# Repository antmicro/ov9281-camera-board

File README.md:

# OV9281 Dual camera board

Copyright (c) 2019-2023 [Antmicro](https://www.antmicro.com)

## Overview

This project contains open hardware design files for a dual camera module equipped with a pair of 1-megapixel [OmniVision OV9281](https://www.ovt.com/sensors/OV9281) image sensors.
The board includes mounting holes for standard S-Mount (M12) lens holders.
Each image sensor can be connected to a host platform via a separate 2-lane MIPI CSI-2 interface.
The PCB design files were prepared in KiCad 6.x.

## Key Features

* Two monochrome global shutter sensors OV9281
 
  * Pixel size: 3μm x 3 μm
  * Active array size: 1280 x 800 px
  * Optical size: 1/4 inch
  * Output formats: 8/10-bit BW RAW
  * Maximum image transfer rate: 1280 x 800 @60 fps

## Project structure 

The  main directory contains KiCad PCB project files, a LICENSE and a README. 
The remaining files are stored in the following directories: 

* `lib` - contains the component libraries 
* `img` - contains graphics for this readme 
* `assets` - contains visual assets for showcasing this design on [Open Hardware Portal](https://openhardware.antmicro.com).

The board exposes MIPI CSI-2 interfaces using unified 50-pin connector that is electrically compatible with a variety of video processing platforms created by Antmicro: 

* [Jeston Orin Baseboard](https://github.com/antmicro/jetson-orin-baseboard)
* [Jetson Nano Baseboard](https://github.com/antmicro/jetson-nano-baseboard)
* [Snapdragon 845 Baseboard](https://github.com/antmicro/snapdragon-845-baseboard)
* [Kria K26 Devboard](https://github.com/antmicro/kria-k26-devboard)

## Licensing

This project is published under the [Apache-2.0](LICENSE) license.

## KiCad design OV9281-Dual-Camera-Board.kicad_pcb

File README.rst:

========================
OV9281 Dual camera board
========================

Copyright (c) 2019-2021 `Antmicro <https://www.antmicro.com>`_

.. Image:: img/ov9281-board-photo.jpg

Overview
========

This repository contains open hardware design files for a dual camera module created by `Antmicro <https://antmicro.com/>`_.
This board is equipped with a pair of 1-megapixel `OmniVision OV9281 <https://www.ovt.com/sensors/OV9281>`_ image sensors with mounting holes for standard S-Mount (M12) lens holders.
Each sensor can be connected to a host platform via a separate 2-lane MIPI CSI-2 interface.
The PCB design files have been written in KiCad and released as Open Source Hardware (OSHW).

Key Features
============

+------------------------------+--------------------------------------+
| Image sensor(s):             | 2 x monochrome global shutter OV9281 |
+------------------------------+--------------------------------------+
| Pixel size:                  | 3μm x 3 μm                           |
+------------------------------+--------------------------------------+
| Active array size:           | 1280 x 800                           |
+------------------------------+--------------------------------------+
| Optical size:                | 1/4 inch                             |
+------------------------------+--------------------------------------+
| Lens mount:                  | M-12 (S-Mount)                       |
+------------------------------+--------------------------------------+
| Output interface:            | 50-pin FFC connector                 |
+------------------------------+--------------------------------------+
| Output formats:              | 8/10-bit BW RAW                      |
+------------------------------+--------------------------------------+
| Maximum image transfer rate: | 1280 x 800 @60 fps                   |
+------------------------------+--------------------------------------+

Interface connector
===================

The board uses a 50-pin FFC connector which exposes two separate MIPI CSI interfaces for both cameras, along with power supply rails and separate I2C buses used for sensor configuration.
The board is electrically compatible with Antmicro's products and open hardware designs, including `Jetson Nano baseboard <https://github.com/antmicro/jetson-nano-baseboard>`_,
`Google Coral Baseboard <https://github.com/antmicro/google-coral-baseboard>`_ or `Zynq Video Board <https://github.com/antmicro/zynq-video-board>`_.

For more details regarding the on-board circuitry please refer to the respective schematic sheets.

Mechanics
=========

Board dimensions:

.. image:: img/ov9281-board-dimensions.png

License
=======

`Apache-2.0 <LICENSE>`_

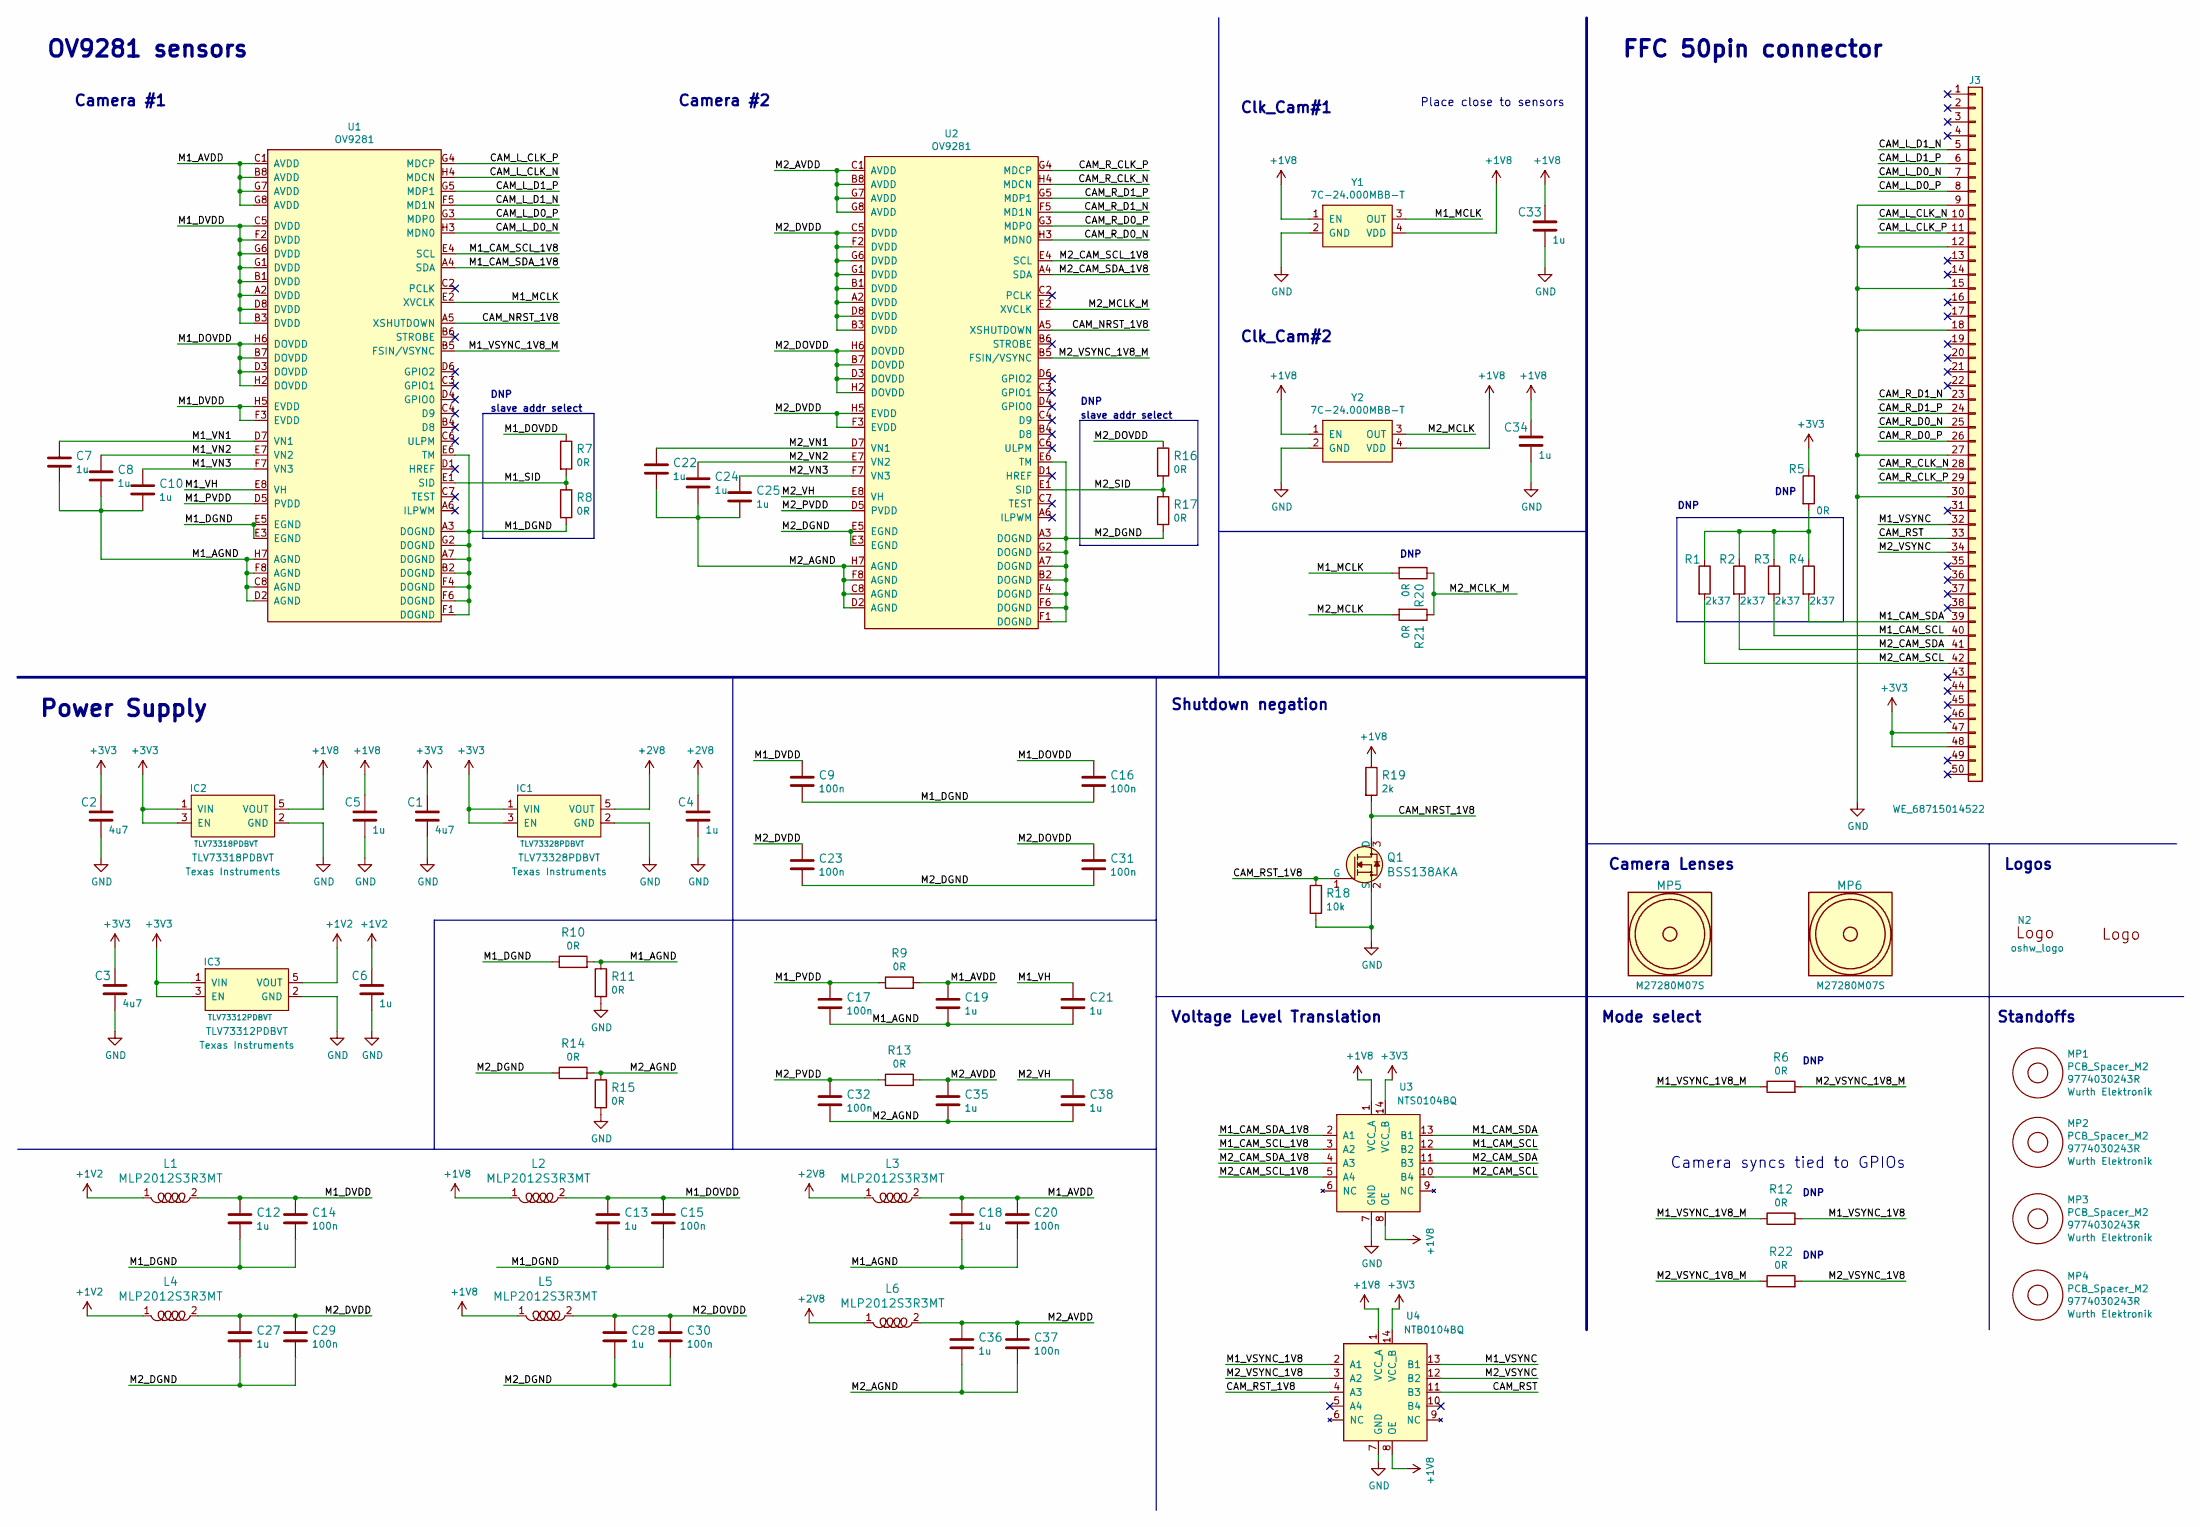
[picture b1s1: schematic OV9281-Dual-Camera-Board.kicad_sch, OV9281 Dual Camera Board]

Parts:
C1, C2, C3: C_4u7_0805; 0805-cap; MPN 0805X475K250CT
C4, C5, C6, C7, C8, C10, C12, C13, C18, C19, C21, C22, C24, C25, C27, C28, C33, C34, C35, C36, C38: C_1u_0603; 0603-cap; MPN 0603X105K160CT
C9, C14, C15, C16, C17, C20, C23, C29, C30, C31, C32, C37: C_100n_0402_6V3; 0402-cap; MPN 0402X104K6R3CT
IC1: TLV73328PDBVT; SOT-23-5; MPN TLV73328PDBVT
IC2: TLV73318PDBVT; SOT-23-5; MPN TLV73318PDBVT
IC3: TLV73312PDBVT; SOT-23-5; MPN TLV73312PDBVT
J3: WE_68715014522; MPN 68715014522
L1, L2, L3, L4, L5, L6: MLP2012S3R3MT; 0805-res; MPN MLP2012S3R3MT
MP1, MP2, MP3, MP4: PCB_Spacer_M2; 9774030243R; MPN 9774030243R
MP5, MP6: Camera_Lens; Camera_Lens_20mm_ARDUCAM_M27280M07S; MPN M27280M07S
N1: antmicro_logo; antmicro-logo_scaled_20mm
N2: oshw_logo; oshw-logo
Q1: BSS138AKA; SOT-23-3; MPN BSS138AKA
R1, R2, R3, R4: R_2k37_0402; 0402-res; MPN CRCW04022K37FKED
R5, R6, R7, R8, R9, R10, R11, R12, R13, R14, R15, R16, R17, R20, R21, R22: R_0R_0402; 0402-res; MPN ERJ2GE0R00X
R18: R_10k_0402; 0402-res; MPN CRCW040210K0FKEDHP
R19: R_2k_0402; 0402-res; MPN CRCW04022K00FKED
U1, U2: OV9281; ov9281; MPN OV9281
U3: NTS0104BQ; QDHVQFN14; MPN NTS0104BQ
U4: NTB0104BQ; QDHVQFN14; MPN NTB0104BQ
Y1, Y2: 7C-24.000MBB-T; MPN 7C-24.000MBB-T

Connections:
+1V2: C6.1, IC3.5 (VOUT), L1.1, L4.1
+1V8: C5.1, C33.1, C34.1, IC2.5 (VOUT), L2.1, L5.1, R19.1, U3.1 (VCC_A), U3.8 (OE), U4.1 (VCC_A), U4.8 (OE), Y1.1 (EN), Y1.4 (VDD), Y2.1 (EN), Y2.4 (VDD)
+2V8: C4.1, IC1.5 (VOUT), L3.1, L6.1
+3V3: C1.1, C2.1, C3.1, IC1.1 (VIN), IC1.3 (EN), IC2.1 (VIN), IC2.3 (EN), IC3.1 (VIN), IC3.3 (EN), J3.47, J3.48, R5.1, U3.14 (VCC_B), U4.14 (VCC_B)
/CAM_L_CLK_N: J3.10, U1.H4 (MDCN)
/CAM_L_CLK_P: J3.11, U1.G4 (MDCP)
/CAM_L_D0_N: J3.7, U1.H3 (MDN0)
/CAM_L_D0_P: J3.8, U1.G3 (MDP0)
/CAM_L_D1_N: J3.5, U1.F5 (MD1N)
/CAM_L_D1_P: J3.6, U1.G5 (MDP1)
/CAM_NRST_1V8: Q1.3 (D), R19.2, U1.A5 (XSHUTDOWN), U2.A5 (XSHUTDOWN)
/CAM_RST: J3.33, U4.11 (B3)
/CAM_RST_1V8: Q1.1 (G), R18.1, U4.4 (A3)
/CAM_R_CLK_N: J3.28, U2.H4 (MDCN)
/CAM_R_CLK_P: J3.29, U2.G4 (MDCP)
/CAM_R_D0_N: J3.25, U2.H3 (MDN0)
/CAM_R_D0_P: J3.26, U2.G3 (MDP0)
/CAM_R_D1_N: J3.23, U2.F5 (MD1N)
/CAM_R_D1_P: J3.24, U2.G5 (MDP1)
/M1_AGND: C7.2, C8.2, C10.2, C17.2, C18.2, C19.2, C20.2, C21.2, R10.2, R11.1, U1.C8 (AGND), U1.D2 (AGND), U1.F8 (AGND), U1.H7 (AGND)
/M1_AVDD: C18.1, C19.1, C20.1, L3.2, R9.2, U1.B8 (AVDD), U1.C1 (AVDD), U1.G7 (AVDD), U1.G8 (AVDD)
/M1_CAM_SCL: J3.40, R3.2, U3.12 (B2)
/M1_CAM_SCL_1V8: U1.E4 (SCL), U3.3 (A2)
/M1_CAM_SDA: J3.39, R4.2, U3.13 (B1)
/M1_CAM_SDA_1V8: U1.A4 (SDA), U3.2 (A1)
/M1_DGND: C9.2, C12.2, C13.2, C14.2, C15.2, C16.2, R8.2, R10.1, U1.A3 (DOGND), U1.A7 (DOGND), U1.B2 (DOGND), U1.E3 (EGND), U1.E5 (EGND), U1.E6 (TM), U1.F1 (DOGND), U1.F4 (DOGND), U1.F6 (DOGND), U1.G2 (DOGND)
/M1_DOVDD: C13.1, C15.1, C16.1, L2.2, R7.1, U1.B7 (DOVDD), U1.D3 (DOVDD), U1.H2 (DOVDD), U1.H6 (DOVDD)
/M1_DVDD: C9.1, C12.1, C14.1, L1.2, U1.A2 (DVDD), U1.B1 (DVDD), U1.B3 (DVDD), U1.C5 (DVDD), U1.D8 (DVDD), U1.F2 (DVDD), U1.F3 (EVDD), U1.G1 (DVDD), U1.G6 (DVDD), U1.H5 (EVDD)
/M1_MCLK: R20.2, U1.E2 (XVCLK), Y1.3 (OUT)
/M1_PVDD: C17.1, R9.1, U1.D5 (PVDD)
/M1_SID: R7.2, R8.1, U1.E1 (SID)
/M1_VH: C21.1, U1.E8 (VH)
/M1_VN1: C7.1, U1.D7 (VN1)
/M1_VN2: C8.1, U1.E7 (VN2)
/M1_VN3: C10.1, U1.F7 (VN3)
/M1_VSYNC: J3.32, U4.13 (B1)
/M1_VSYNC_1V8: R12.2, U4.2 (A1)
/M1_VSYNC_1V8_M: R6.1, R12.1, U1.B5 (FSIN/VSYNC)
/M2_AGND: C22.2, C24.2, C25.2, C32.2, C35.2, C36.2, C37.2, C38.2, R14.2, R15.1, U2.C8 (AGND), U2.D2 (AGND), U2.F8 (AGND), U2.H7 (AGND)
/M2_AVDD: C35.1, C36.1, C37.1, L6.2, R13.2, U2.B8 (AVDD), U2.C1 (AVDD), U2.G7 (AVDD), U2.G8 (AVDD)
/M2_CAM_SCL: J3.42, R1.2, U3.10 (B4)
/M2_CAM_SCL_1V8: U2.E4 (SCL), U3.5 (A4)
/M2_CAM_SDA: J3.41, R2.2, U3.11 (B3)
/M2_CAM_SDA_1V8: U2.A4 (SDA), U3.4 (A3)
/M2_DGND: C23.2, C27.2, C28.2, C29.2, C30.2, C31.2, R14.1, R17.2, U2.A3 (DOGND), U2.A7 (DOGND), U2.B2 (DOGND), U2.E3 (EGND), U2.E5 (EGND), U2.E6 (TM), U2.F1 (DOGND), U2.F4 (DOGND), U2.F6 (DOGND), U2.G2 (DOGND)
/M2_DOVDD: C28.1, C30.1, C31.1, L5.2, R16.1, U2.B7 (DOVDD), U2.D3 (DOVDD), U2.H2 (DOVDD), U2.H6 (DOVDD)
/M2_DVDD: C23.1, C27.1, C29.1, L4.2, U2.A2 (DVDD), U2.B1 (DVDD), U2.B3 (DVDD), U2.C5 (DVDD), U2.D8 (DVDD), U2.F2 (DVDD), U2.F3 (EVDD), U2.G1 (DVDD), U2.G6 (DVDD), U2.H5 (EVDD)
/M2_MCLK: R21.2, Y2.3 (OUT)
/M2_MCLK_M: R20.1, R21.1, U2.E2 (XVCLK)
/M2_PVDD: C32.1, R13.1, U2.D5 (PVDD)
/M2_SID: R16.2, R17.1, U2.E1 (SID)
/M2_VH: C38.1, U2.E8 (VH)
/M2_VN1: C22.1, U2.D7 (VN1)
/M2_VN2: C24.1, U2.E7 (VN2)
/M2_VN3: C25.1, U2.F7 (VN3)
/M2_VSYNC: J3.34, U4.12 (B2)
/M2_VSYNC_1V8: R22.2, U4.3 (A2)
/M2_VSYNC_1V8_M: R6.2, R22.1, U2.B5 (FSIN/VSYNC)
GND: C1.2, C2.2, C3.2, C4.2, C5.2, C6.2, C33.2, C34.2, IC1.2 (GND), IC2.2 (GND), IC3.2 (GND), J3.9, J3.12, J3.15, J3.18, J3.27, J3.30, Q1.2 (S), R11.2, R15.2, R18.2, U3.7 (GND), U4.7 (GND), Y1.2 (GND), Y2.2 (GND)
unnamed: R1.1, R2.1, R3.1, R4.1, R5.2

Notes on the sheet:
DNP
Voltage Level Translation
FFC 50pin connector
slave addr select
Power Supply
Place close to sensors
Shutdown negation
Clk_Cam#2
Camera #1
Camera Lenses
Camera #2
Standoffs
Mode select
Logos
Camera syncs tied to GPIOs
OV9281 sensors
Clk_Cam#1

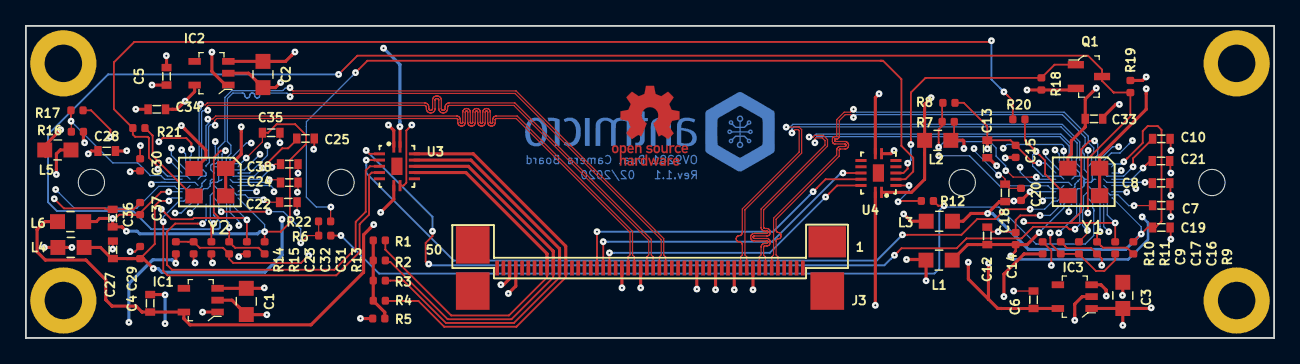
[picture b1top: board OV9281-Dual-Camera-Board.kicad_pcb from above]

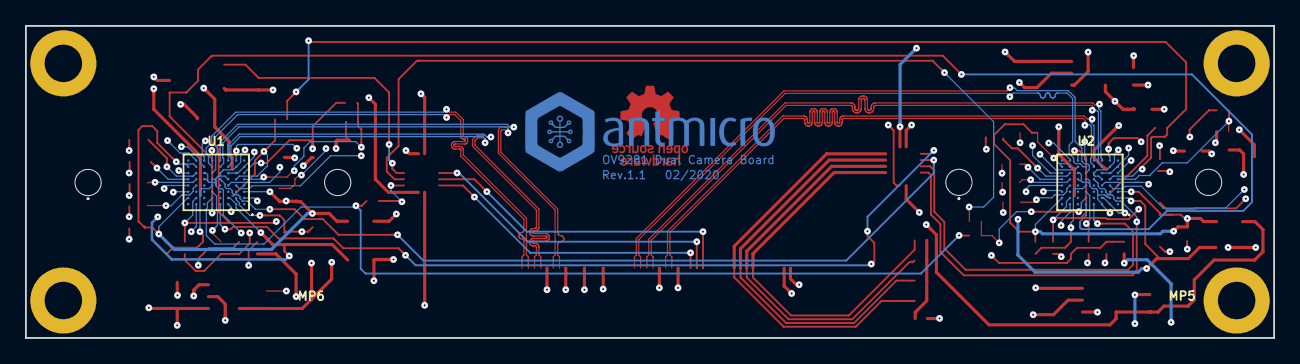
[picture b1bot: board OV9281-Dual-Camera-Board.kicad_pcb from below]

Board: 4 copper layers, 100.0 x 25.0 mm, 83 parts (5 on the bottom side), 60 nets.

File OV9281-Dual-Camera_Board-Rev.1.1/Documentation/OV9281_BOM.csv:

Item,Qty,Reference(s),Value,Footprint,MPN,Manufacturer
1,3,"C1, C2, C3, ",C_4u7_0805,antmicro-footprints:0805-cap,0805X475K250CT,WALSIN
2,21,"C4, C5, C6, C7, C8, C10, C12, C13, C18, C19, C21, C22, C24, C25, C27, C28, C33, C34, C35, C36, C38, ",C_1u_0603,antmicro-footprints:0603-cap,0603X105K160CT,WALSIN
3,12,"C9, C14, C15, C16, C17, C20, C23, C29, C30, C31, C32, C37, ",C_100n_0402_6V3,antmicro-footprints:0402-cap,0402X104K6R3CT,Walsin
4,1,"IC1, ",TLV73328PDBVT,antmicro-footprints:SOT-23-5,TLV73328PDBVT,Texas Instruments
5,1,"IC2, ",TLV73318PDBVT,antmicro-footprints:SOT-23-5,TLV73318PDBVT,Texas Instruments
6,1,"IC3, ",TLV73312PDBVT,antmicro-footprints:SOT-23-5,TLV73312PDBVT,Texas Instruments
7,1,"J3, ",WE_68715014522,antmicro-footprints:WE_68715014522,68715014522,Wurth ELEKTRONIK
8,6,"L1, L2, L3, L4, L5, L6, ",MLP2012S3R3MT,antmicro-footprints:0805-res,MLP2012S3R3MT,TDK
9,4,"MP1, MP2, MP3, MP4, ",PCB_Spacer_M2,antmicro-footprints:9774030243R,9774030243R,Wurth Elektronik 
10,1,"Q1, ",BSS138AKA,antmicro-footprints:SOT-23-3,BSS138AKA,ON Semiconductor
11,11,"R7, R8, R9, R10, R11, R13, R14, R15, R16, R17, R21, ",R_0R_0402,antmicro-footprints:0402-res,ERJ2GE0R00X,PANASONIC
12,1,"R18, ",R_10k_0402,antmicro-footprints:0402-res,CRCW040210K0FKEDHP,VISHAY
13,1,"R19, ",R_2k_0402,antmicro-footprints:0402-res,CRCW04022K00FKED,VISHAY
14,2,"U1, U2, ",OV9281,antmicro-footprints:ov9281,OV9281,OmniVision
15,1,"U3, ",NTS0104BQ,antmicro-footprints:QDHVQFN14,NTS0104BQ,NXP Semiconductors
16,1,"U4, ",NTB0104BQ,antmicro-footprints:QDHVQFN14,NTB0104BQ,NXP Semiconductors
17,2,"Y1, Y2, ",7C-24.000MBB-T,antmicro-footprints:7C-24.000MBB-T,7C-24.000MBB-T,TXC

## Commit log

2020-03-06 Defined initial component placement
2020-03-06 Pick and Place merged into a single file
2020-03-06 Moved some low speed signal tracks
2020-03-06 Minor changes
2020-03-06 PCB routing
2020-03-06 Edited design rules to make bigger clearance
2020-03-06 PCB ready for manufacturing
2020-03-06 Cleanup
2020-03-06 Updated transistor and inductors from libraries
2020-03-06 Added mounting holes for lenses
2020-03-06 Unified power rails, added power supply filters
2020-03-06 Added voltage level translation
2020-03-06 Started rev.1.1, added resistors for choosing VSYNC connection
2020-03-06 Unified file names and references
2020-03-06 Updated virtual components on PCB
2020-03-06 Added OSHW logo, updated hole spacing for lens mount
2020-03-06 Updated file structure
2020-03-06 Minor fix
2020-03-06 Updated project structure
2020-03-06 README updated key features
2020-03-06 Added LICENSE
2020-03-09 Fixed logotypes, exported new schematics PDF
2021-03-09 Bump revision to 1.1.0
2021-03-09 Update LICENSE
2021-04-30 Fix typo
2021-06-24 Notes added by 'git notes add'
2023-09-15 Improve camera lenses
2023-09-15 Update symbols
2023-09-15 Update TLV33P28 symbol
2023-09-15 Fix DNP
2023-09-15 Update TLV3318 to standardized version
2023-09-15 Fix DRC
2023-09-15 Update OV9281
2023-09-21 [#49221] Standardize schematic's symbols
2023-09-21 [#49221] Update PCB design
2023-09-22 [#49221] Replace BSS138PW with standardized BSS138AKA symbol
2023-09-22 [#49221] Update PCB design
    Optimize/correct routing and component placement
    Fix DRC errors
    Organise silkscreen layers
    Correct CAM_L_D0 skew
2023-09-22 [#49221] Add "PCB SHA ########" to the F.Silk
2023-09-22 [#49221] Replace QDHVQFN14 footprint with DHVQFN-14_1EP_2.5x3mm In NTS0104BQ and NTB0104BQ symbols
2023-09-22 [#49221] Bump revision to 1.1.1
2023-09-25 [#49221] Update symbols and add fiducials
2023-09-25 [#49221] Add ERC exclusion
    Add Bi-directional pin connected to Power-out ERC warning to exclusions
2023-09-25 [#49221] Update footprints and add fiducials
2023-09-25 [#49221] Hide spacers' Ref and update bottom silkscreen
2023-09-26 [#49221] Update ImageSensor_OV9281 footprint
2023-10-12 Removed old kicad 5 files
2023-10-12 Improved layout for signal integrity [#50177]
2023-10-13 Routing improvements [#50177]
2023-10-13 Fixed schematic issues [#50177]
2023-10-13 Length matched CSI traces [#50177]
2023-11-07 Fixed overlapping text on the schematic
2023-11-07 Update ignore
2023-11-07 README: re-write into MD
2023-11-07 README: update images
2023-11-07 Update revision marking
2023-11-07 Add OHP assets
2023-11-08 Update project files to generate stackup data properly
2023-11-08 Reupload OHP assets
2023-11-23 Update FFC connector and standoffs
2023-11-24 Update components from library
2023-11-24 Update components from libraries
2023-11-27 Fix designators
2023-11-27 Bump revision to 1.1.2
2023-11-27 Fixes after review
2023-11-27 Update assets
